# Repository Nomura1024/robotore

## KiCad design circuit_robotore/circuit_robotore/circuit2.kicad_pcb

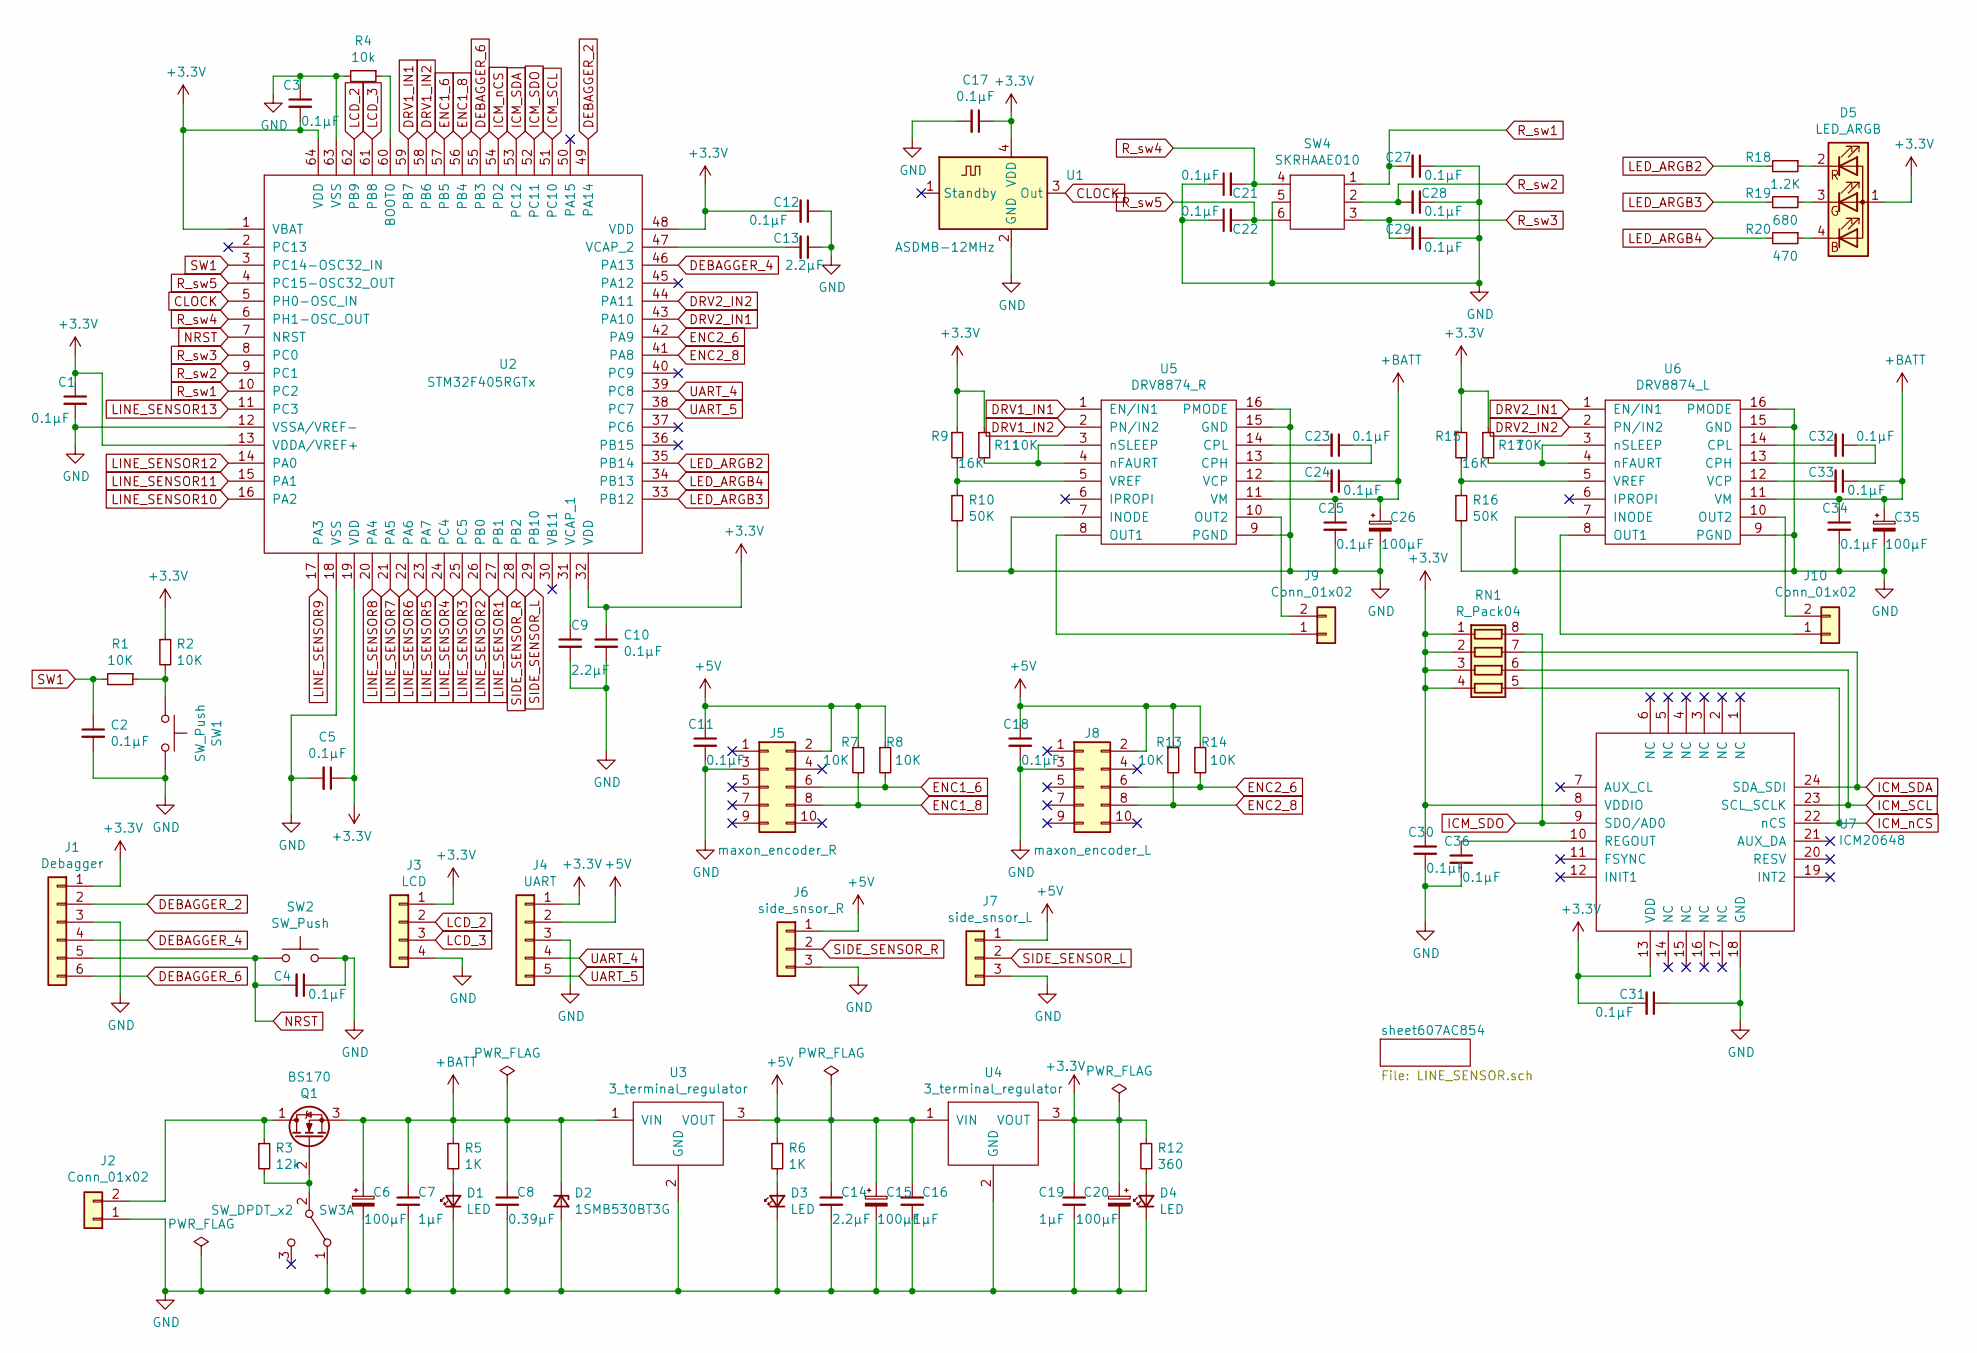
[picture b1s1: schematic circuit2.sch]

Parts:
C1, C2, C3, C4, C5, C10, C11, C12, C17, C18, C21, C22, C23, C24, C25, C27, C28, C29, C30, C31, C32, C33, C34, C36: 0.1μF; C_0603_1608Metric
C6, C15, C20, C26, C35: 100μF; CP_EIA-7132-20_AVX-U
C7, C16, C19: 1μF; C_0603_1608Metric
C8: 0.39μF; C_0603_1608Metric
C9, C13, C14: 2.2μF; C_0603_1608Metric
D1, D3, D4: LED; LED_0603_1608Metric_Castellated
D2: 1SMB530BT3G; 1SMB5930BT3G
D5: LED_ARGB; LED_LiteOn_LTST-C19HE1WT
J1: Debagger; JST_SH_BM06B-SRSS-TB_1x06-1MP_P1.00mm_Vertical
J2, J9, J10: Conn_01x02; PA_2pin
J3: LCD; JST_SH_BM04B-SRSS-TB_1x04-1MP_P1.00mm_Vertical
J4: UART; JST_SH_BM05B-SRSS-TB_1x05-1MP_P1.00mm_Vertical
J5: maxon_encoder_R; PinSocket_2x05_P1.27mm_Vertical
J6: side_snsor_R; JST_SH_BM03B-SRSS-TB_1x03-1MP_P1.00mm_Vertical
J7: side_snsor_L; JST_SH_BM03B-SRSS-TB_1x03-1MP_P1.00mm_Vertical
J8: maxon_encoder_L; PinSocket_2x05_P1.27mm_Vertical
Q1: BS170; uPA2815T1S
R1, R2, R7, R8, R11, R13, R14, R17: 10K; R_0603_1608Metric
R3: 12k; R_0603_1608Metric
R4: 10k; R_0603_1608Metric
R5, R6: 1K; R_0603_1608Metric
R9, R15: 16K; R_0603_1608Metric
R10, R16: 50K; R_0603_1608Metric
R12: 360; R_0603_1608Metric
R18: 1.2K; R_0603_1608Metric
R19: 680; R_0603_1608Metric
R20: 470; R_0603_1608Metric
RN1: R_Pack04; R_Array_Convex_4x1206
SW1, SW2: SW_Push; R_2010_5025Metric
SW3: SW_DPDT_x2; Nidec_Copal_SH-7010A
SW4: SKRHAAE010
U1: ASDMB-12MHz; Oscillator_SMD_Abracon_ASDMB-4Pin_2.5x2.0mm
U2: STM32F405RGTx; LQFP-64_10x10mm_P0.5mm
U3, U4: 3_terminal_regulator; SOT-223-3_TabPin2
U5: DRV8874_R; HTSSOP-16-1EP_4.4x5mm_P0.65mm_EP3.4x5mm
U6: DRV8874_L; HTSSOP-16-1EP_4.4x5mm_P0.65mm_EP3.4x5mm
U7: ICM20648

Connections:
+3V3: C1.1, C3.2, C5.1, C10.1, C12.2, C17.1, C19.1, C20.1, C30.1, C31.2, D5.1 (A), J1.1, J3.1, J4.1, R2.1, R9.1, R11.1, R12.1, R15.1, R17.1, RN1.1 (R1.1), RN1.2 (R2.1), RN1.3 (R3.1), RN1.4 (R4.1), U1.4 (VDD), U2.1 (VBAT), U2.13 (VDDA/VREF+), U2.19 (VDD), U2.32 (VDD), U2.48 (VDD), U2.64 (VDD), U4.3 (VOUT), U7.8 (VDDIO), U7.13 (VDD); also elsewhere on the board
+5V: C11.1, C14.1, C15.1, C16.1, C18.1, J4.2, J5.2, J6.1, J7.1, J8.2, R6.1, R7.1, R8.1, R13.1, R14.1, U3.3 (VOUT), U4.1 (VIN)
+BATT: C6.1, C7.1, C8.1, C24.1, C25.1, C26.1, C33.1, C34.1, C35.1, D2.1 (K), Q1.3 (S), R5.1, U3.1 (VIN), U5.11 (VM), U6.11 (VM)
CLOCK: U1.3 (Out), U2.5 (PH0-OSC_IN)
DEBAGGER_2: J1.2, U2.49 (PA14)
DEBAGGER_4: J1.4, U2.46 (PA13)
DEBAGGER_6: J1.6, U2.55 (PB3)
DRV1_IN1: U2.59 (PB7), U5.1 (EN/IN1)
DRV1_IN2: U2.58 (PB6), U5.2 (PN/IN2)
DRV2_IN1: U2.43 (PA10), U6.1 (EN/IN1)
DRV2_IN2: U2.44 (PA11), U6.2 (PN/IN2)
ENC1_6: J5.6, R8.2, U2.57 (PB5)
ENC1_8: J5.8, R7.2, U2.56 (PB4)
ENC2_6: J8.6, R14.2, U2.42 (PA9)
ENC2_8: J8.8, R13.2, U2.41 (PA8)
GND: C1.2, C2.2, C3.1, C4.1, C5.2, C6.2, C7.2, C8.2, C9.2, C10.2, C11.2, C12.1, C13.1, C14.2, C15.2, C16.2, C17.2, C18.2, C19.2, C20.2, C21.1, C22.1, C25.2, C26.2, C27.1, C28.1, C29.1, C30.2, C31.1, C34.2, C35.2, C36.2, D1.1 (K), D2.2 (A), D3.1 (K), D4.1 (K), J1.3, J2.1, J3.4, J4.3, J5.3, J6.3, J7.3, J8.3, R4.2, R10.2, R16.2, SW1.2, SW2.2, SW3.1 (A), SW4.5, U1.2 (GND), U2.12 (VSSA/VREF-), U2.18 (VSS), U2.63 (VSS), U3.2 (GND), U4.2 (GND), U5.7 (INODE), U5.9 (PGND), U5.15 (GND), U5.16 (PMODE), U6.7 (INODE), U6.9 (PGND), U6.15 (GND), U6.16 (PMODE), U7.18 (GND); also elsewhere on the board
ICM_SCL: RN1.6 (R3.2), U2.51 (PC10), U7.23 (SCL_SCLK)
ICM_SDA: RN1.7 (R2.2), U2.53 (PC12), U7.24 (SDA_SDI)
ICM_SDO: RN1.8 (R1.2), U2.52 (PC11), U7.9 (SDO/AD0)
ICM_nCS: RN1.5 (R4.2), U2.54 (PD2), U7.22 (nCS)
LCD_2: J3.2, U2.62 (PB9)
LCD_3: J3.3, U2.61 (PB8)
LED_ARGB2: R18.2, U2.35 (PB14)
LED_ARGB3: R19.2, U2.33 (PB12)
LED_ARGB4: R20.2, U2.34 (PB13)
LINE_SENSOR1: U2.27 (PB1); also elsewhere on the board
LINE_SENSOR2: U2.26 (PB0); also elsewhere on the board
LINE_SENSOR3: U2.25 (PC5); also elsewhere on the board
LINE_SENSOR4: U2.24 (PC4); also elsewhere on the board
LINE_SENSOR5: U2.23 (PA7); also elsewhere on the board
LINE_SENSOR6: U2.22 (PA6); also elsewhere on the board
LINE_SENSOR7: U2.21 (PA5); also elsewhere on the board
LINE_SENSOR8: U2.20 (PA4); also elsewhere on the board
LINE_SENSOR9: U2.17 (PA3); also elsewhere on the board
LINE_SENSOR10: U2.16 (PA2); also elsewhere on the board
LINE_SENSOR11: U2.15 (PA1); also elsewhere on the board
LINE_SENSOR12: U2.14 (PA0); also elsewhere on the board
LINE_SENSOR13: U2.11 (PC3); also elsewhere on the board
NRST: C4.2, J1.5, SW2.1, U2.7 (NRST)
unnamed: C9.1, U2.31 (VCAP_1)
unnamed: C13.2, U2.47 (VCAP_2)
unnamed: C23.1, U5.13 (CPH)
unnamed: C23.2, U5.14 (CPL)
unnamed: C24.2, U5.12 (VCP)
unnamed: C32.1, U6.13 (CPH)
unnamed: C32.2, U6.14 (CPL)
unnamed: C33.2, U6.12 (VCP)
unnamed: C36.1, U7.10 (REGOUT)
unnamed: D1.2 (A), R5.2
unnamed: D3.2 (A), R6.2
unnamed: D4.2 (A), R12.2
unnamed: D5.2 (RK), R18.1
unnamed: D5.3 (GK), R19.1
unnamed: D5.4 (BK), R20.1
unnamed: J2.2, Q1.1 (D), R3.1
unnamed: J9.1, U5.8 (OUT1)
unnamed: J9.2, U5.10 (OUT2)
unnamed: J10.1, U6.8 (OUT1)
unnamed: J10.2, U6.10 (OUT2)
unnamed: Q1.2 (G), R3.2, SW3.2 (B)
unnamed: R1.1, R2.2, SW1.1
unnamed: R4.1, U2.60 (BOOT0)
unnamed: R9.2, R10.1, U5.5 (VREF)
unnamed: R11.2, U5.3 (nSLEEP), U5.4 (nFAURT)
unnamed: R15.2, R16.1, U6.5 (VREF)
unnamed: R17.2, U6.3 (nSLEEP), U6.4 (nFAURT)
R_sw1: C27.2, SW4.1, U2.10 (PC2)
R_sw2: C28.2, SW4.2, U2.9 (PC1)
R_sw3: C29.2, SW4.3, U2.8 (PC0)
R_sw4: C21.2, SW4.4, U2.6 (PH1-OSC_OUT)
R_sw5: C22.2, SW4.6, U2.4 (PC15-OSC32_OUT)
SIDE_SENSOR_L: J7.2, U2.29 (PB10)
SIDE_SENSOR_R: J6.2, U2.28 (PB2)
SW1: C2.1, R1.2, U2.3 (PC14-OSC32_IN)
UART_4: J4.4, U2.39 (PC8)
UART_5: J4.5, U2.38 (PC7)

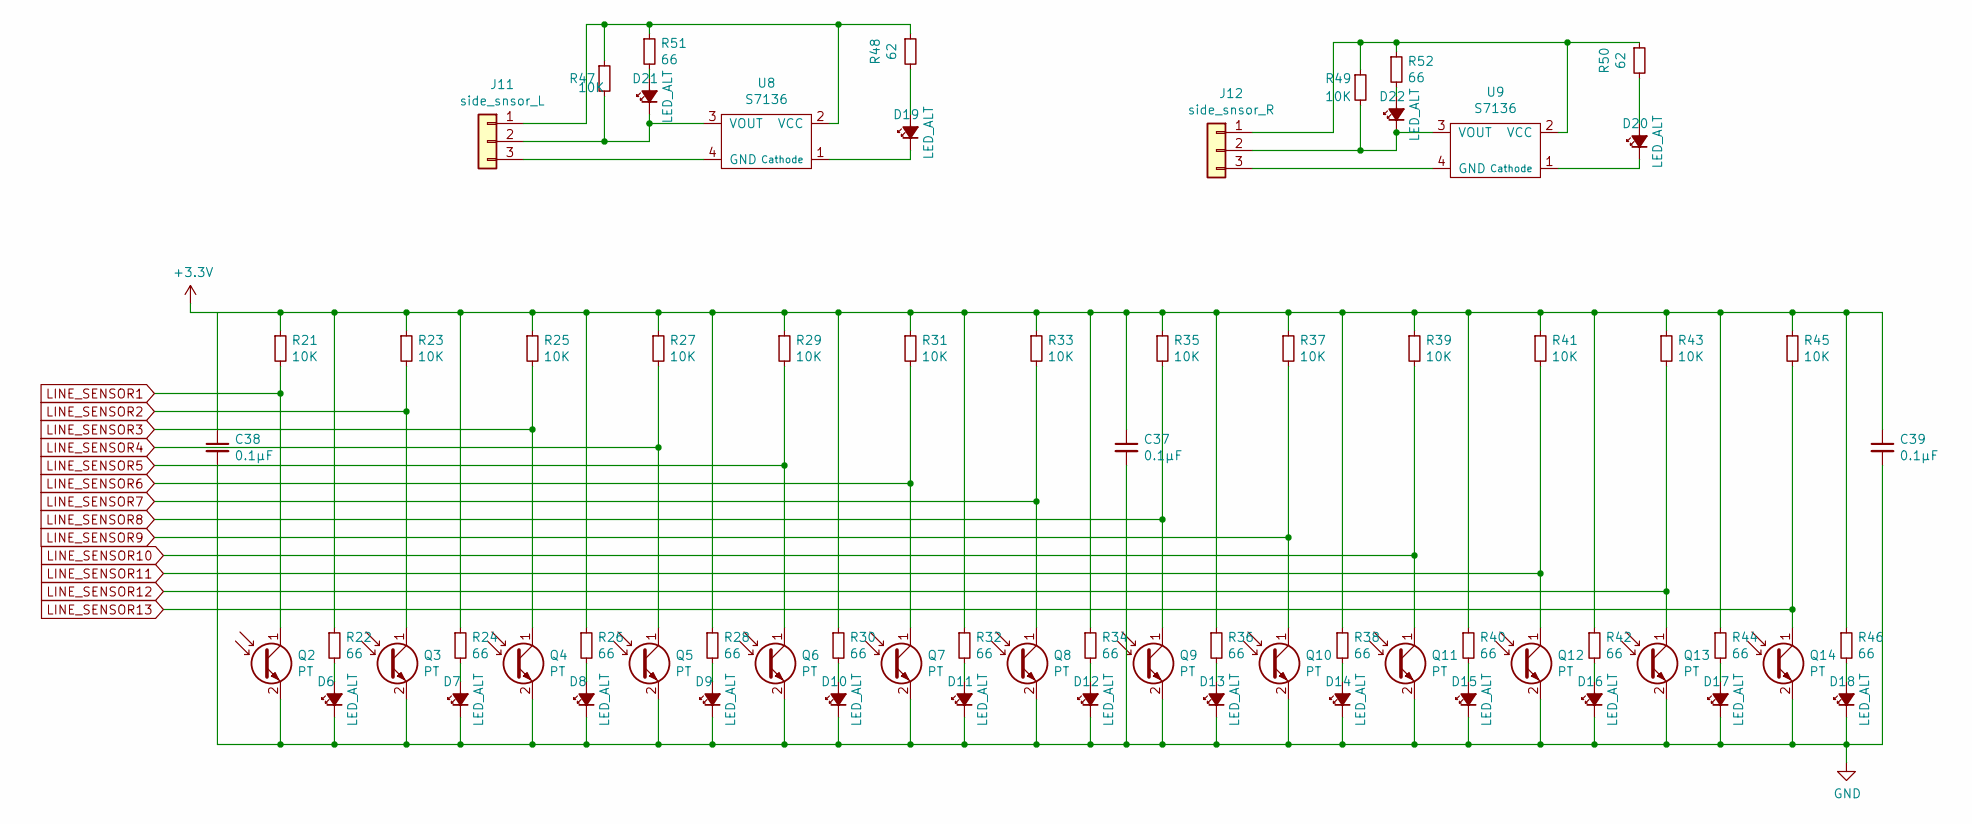
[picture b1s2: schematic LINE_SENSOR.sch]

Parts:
C37, C38, C39: 0.1μF; C_0603_1608Metric
D6, D7, D8, D9, D10, D11, D12, D13, D14, D15, D16, D17, D18, D19, D20, D21, D22: LED_ALT; LED_0603_1608Metric_Castellated
J11: side_snsor_L; JST_SH_BM03B-SRSS-TB_1x03-1MP_P1.00mm_Vertical
J12: side_snsor_R; JST_SH_BM03B-SRSS-TB_1x03-1MP_P1.00mm_Vertical
Q2, Q3, Q4, Q5, Q6, Q7, Q8, Q9, Q10, Q11, Q12, Q13, Q14: PT; C_0603_1608Metric_Pad1.08x0.95mm_HandSolder
R21, R23, R25, R27, R29, R31, R33, R35, R37, R39, R41, R43, R45, R47, R49: 10K; R_0603_1608Metric
R22, R24, R26, R28, R30, R32, R34, R36, R38, R40, R42, R44, R46, R51, R52: 66; R_0603_1608Metric
R48, R50: 62; R_0603_1608Metric
U8, U9: S7136

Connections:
+3V3: C37.1, C39.1, R21.1, R22.1, R23.1, R24.1, R25.1, R26.1, R27.1, R28.1, R29.1, R30.1, R31.1, R32.1, R33.1, R34.1, R35.1, R36.1, R37.1, R38.1, R39.1, R40.1, R41.1, R42.1, R43.1, R44.1, R45.1, R46.1; also elsewhere on the board
GND: C37.2, C38.2, C39.2, D6.1 (K), D7.1 (K), D8.1 (K), D9.1 (K), D10.1 (K), D11.1 (K), D12.1 (K), D13.1 (K), D14.1 (K), D15.1 (K), D16.1 (K), D17.1 (K), D18.1 (K), Q2.2 (E), Q3.2 (E), Q4.2 (E), Q5.2 (E), Q6.2 (E), Q7.2 (E), Q8.2 (E), Q9.2 (E), Q10.2 (E), Q11.2 (E), Q12.2 (E), Q13.2 (E), Q14.2 (E); also elsewhere on the board
LINE_SENSOR1: Q2.1 (C), R21.2; also elsewhere on the board
LINE_SENSOR2: Q3.1 (C), R23.2; also elsewhere on the board
LINE_SENSOR3: Q4.1 (C), R25.2; also elsewhere on the board
LINE_SENSOR4: Q5.1 (C), R27.2; also elsewhere on the board
LINE_SENSOR5: Q6.1 (C), R29.2; also elsewhere on the board
LINE_SENSOR6: Q7.1 (C), R31.2; also elsewhere on the board
LINE_SENSOR7: Q8.1 (C), R33.2; also elsewhere on the board
LINE_SENSOR8: Q9.1 (C), R35.2; also elsewhere on the board
LINE_SENSOR9: Q10.1 (C), R37.2; also elsewhere on the board
LINE_SENSOR10: Q11.1 (C), R39.2; also elsewhere on the board
LINE_SENSOR11: Q12.1 (C), R41.2; also elsewhere on the board
LINE_SENSOR12: Q13.1 (C), R43.2; also elsewhere on the board
LINE_SENSOR13: Q14.1 (C), R45.2; also elsewhere on the board
unnamed: D6.2 (A), R22.2
unnamed: D7.2 (A), R24.2
unnamed: D8.2 (A), R26.2
unnamed: D9.2 (A), R28.2
unnamed: D10.2 (A), R30.2
unnamed: D11.2 (A), R32.2
unnamed: D12.2 (A), R34.2
unnamed: D13.2 (A), R36.2
unnamed: D14.2 (A), R38.2
unnamed: D15.2 (A), R40.2
unnamed: D16.2 (A), R42.2
unnamed: D17.2 (A), R44.2
unnamed: D18.2 (A), R46.2
unnamed: D19.1 (K), U8.1 (Cathode)
unnamed: D19.2 (A), R48.2
unnamed: D20.1 (K), U9.1 (Cathode)
unnamed: D20.2 (A), R50.2
unnamed: D21.1 (K), J11.2, R47.2, U8.3 (VOUT)
unnamed: D21.2 (A), R51.2
unnamed: D22.1 (K), J12.2, R49.2, U9.3 (VOUT)
unnamed: D22.2 (A), R52.2
unnamed: J11.1, R47.1, R48.1, R51.1, U8.2 (VCC)
unnamed: J11.3, U8.4 (GND)
unnamed: J12.1, R49.1, R50.1, R52.1, U9.2 (VCC)
unnamed: J12.3, U9.4 (GND)

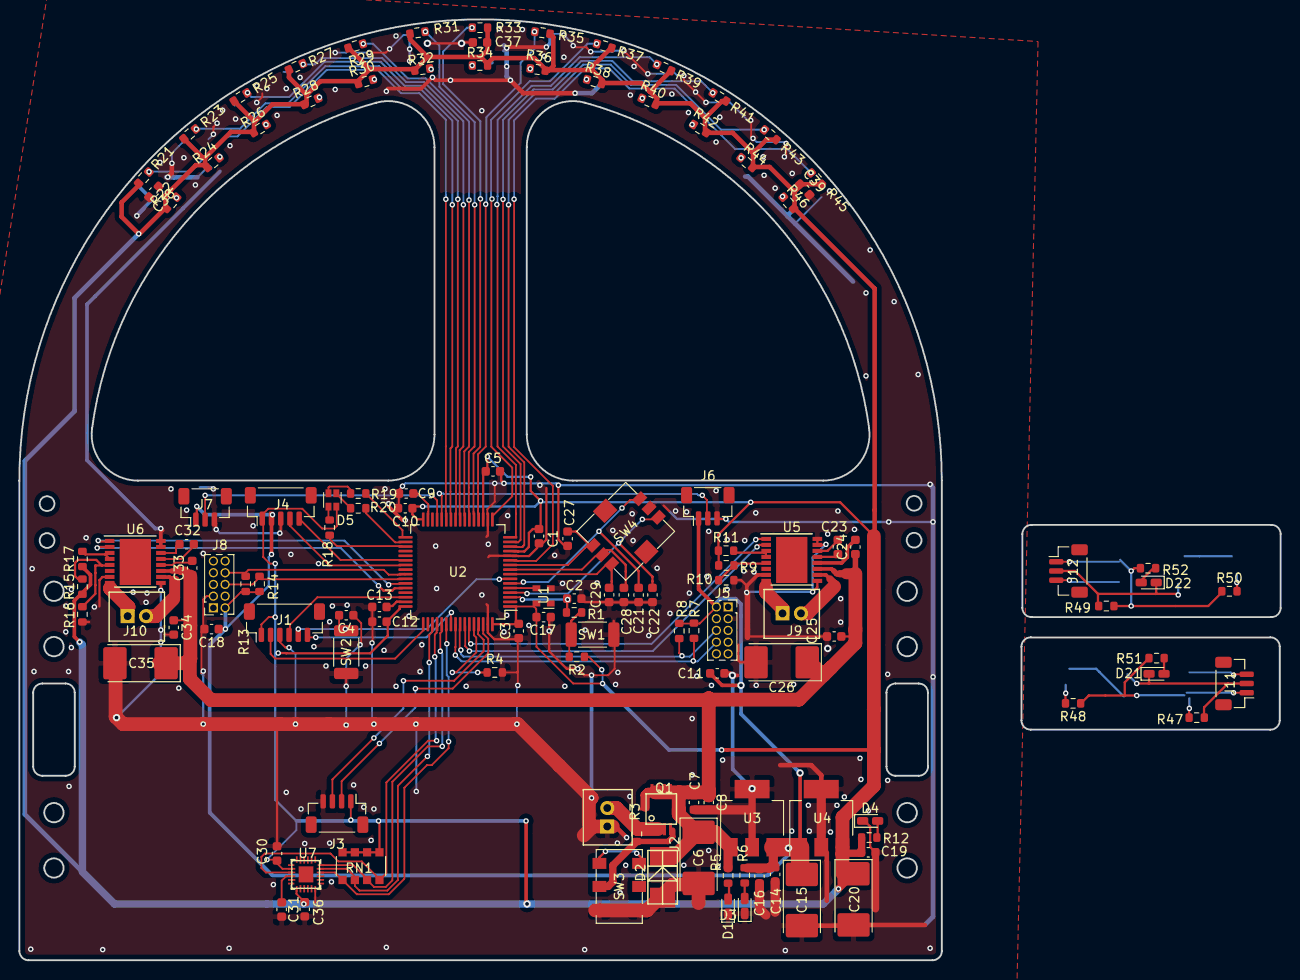
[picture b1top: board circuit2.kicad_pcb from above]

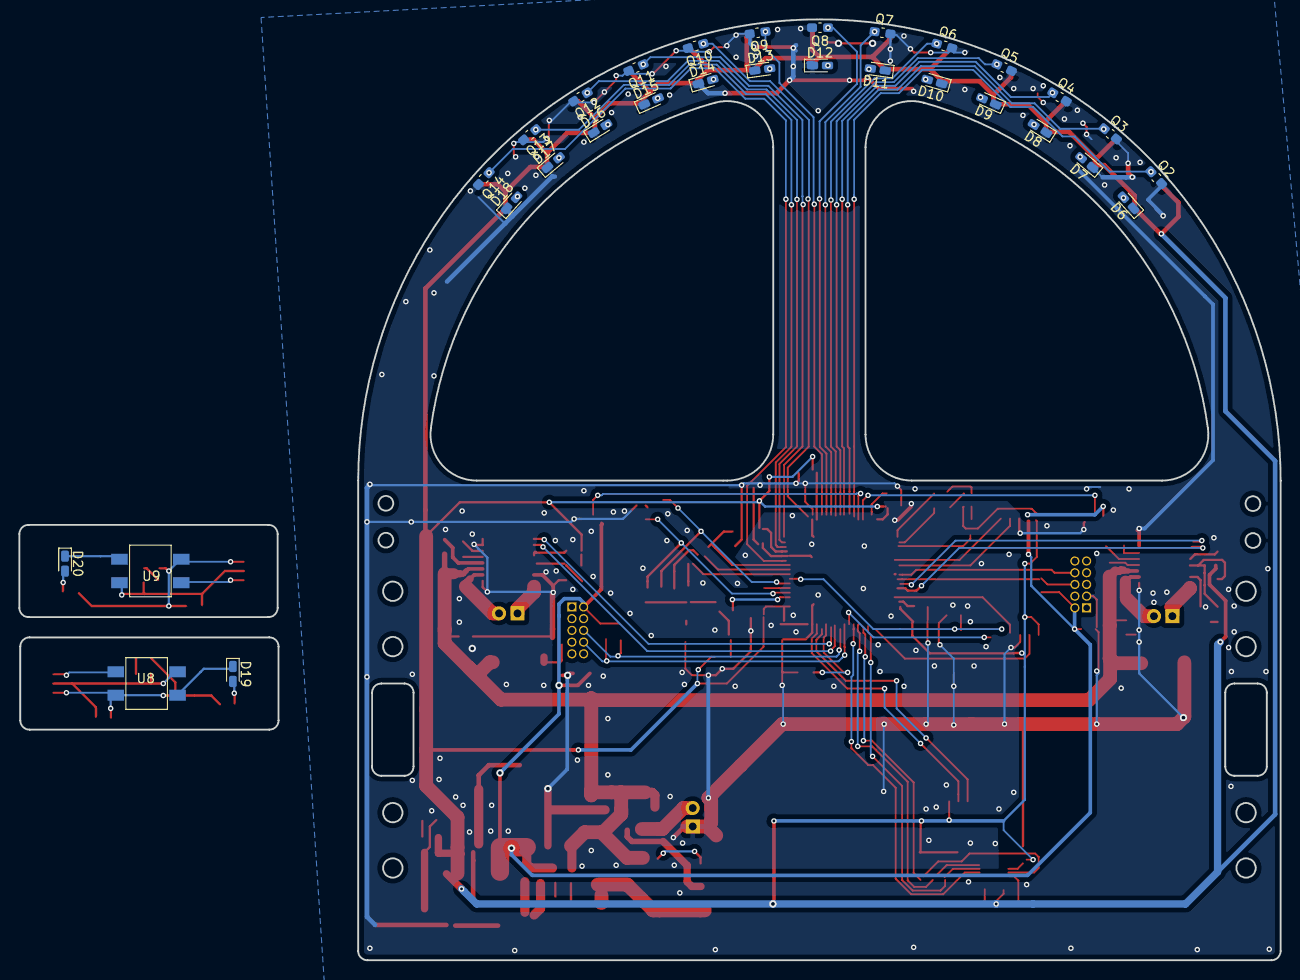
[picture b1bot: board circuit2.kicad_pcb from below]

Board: 2 copper layers, 136.7 x 102.0 mm, 153 parts (30 on the bottom side), 101 nets.

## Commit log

2021-05-03 init
